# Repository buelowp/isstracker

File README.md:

# Use an opaque globe to show the position of the ISS using a laser
This project is going to project the ISS location on a globe showing current position continuously. The system uses a Particle Argon, one stepper motor for longitude rotation, and one servo motor for latitude rotation. It also uses a LOT of other parts listed in the BOM to make this work.

The goal is to provide a good looking device that is accurate and consistent. All of the motors and electronics must be hidden, and all parts must be independently moveable. So, the globe must be able to rotate without changing where the laser is pointing. The laser must work inside the globe independent of the base. The laser must also rotate 360 degrees longitude. The ISS does not go above or below ~60 degrees latitude, so a simple servo can be used for that.

A Particle project named isstracker

I found a similar project using an ESP8266 about 5 years ago and I was intrigued. So, I started hacking something up, but my requirements became much more complex than the original project. I wanted full rotation and to be able to *spin* the globe sitting on a base without changing where the location of the point showing the ISS.

It uses two independent sliprings which provide the ability to rotate the globe and the armature holding the laser without losing precision. It uses one 200 step NEMA stepper for longitude, and one 160 degree servo for the latitiude. The laser is from Sparkfun, but any laser that can be powered by 3 volts would work.

Pictures to follow

## Building it

Instructions to follow

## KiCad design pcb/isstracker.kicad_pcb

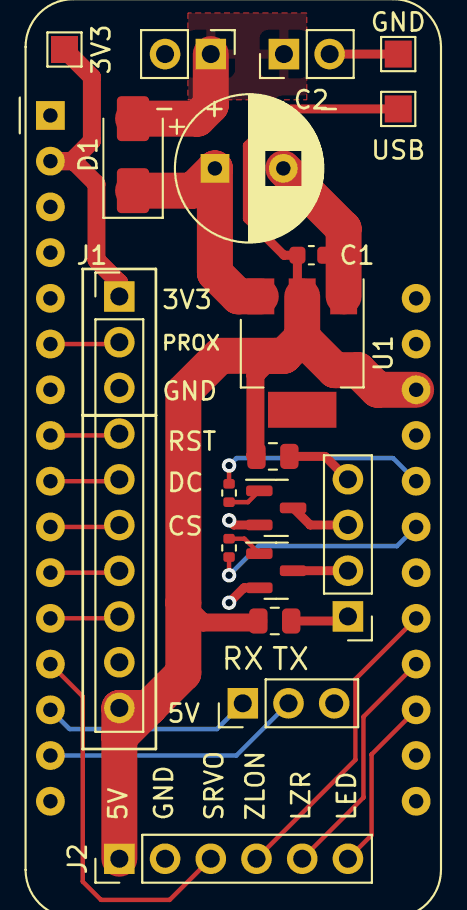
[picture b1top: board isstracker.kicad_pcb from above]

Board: 2 copper layers, 20 parts (0 on the bottom side), 25 nets.

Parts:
A1: Adafruit_Feather_Generic; Adafruit_Feather
C1: 220pf; C_0603_1608Metric
C2: 330uf; CP_Radial_D8.0mm_P3.80mm
D1: D_Schottky; D_SMA
J1: Display; PinHeader_1x10_P2.54mm_Vertical
J2: Control; PinHeader_1x06_P2.54mm_Vertical
J3: POWER; PinHeader_1x02_P2.54mm_Vertical
J4: Error LED; PinHeader_1x04_P2.54mm_Vertical
J5: POWER_OUT; PinHeader_1x02_P2.54mm_Vertical
J6: Conn_01x03_Pin; PinHeader_1x03_P2.54mm_Vertical
Q1, Q2: MMBT2222A; SOT-23
R1, R2: 1k; R_0402_1005Metric
R3, R4: 1k; R_0805_2012Metric
TP1: USB; TestPoint_Pad_1.5x1.5mm
TP2: GND; TestPoint_Pad_1.5x1.5mm
TP3: 3V3; TestPoint_Pad_1.5x1.5mm
U1: CJT1117-5.0; SOT-223

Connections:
+3V3: A1.2 (3V3), J1.1, TP3.1
CS: A1.10 (A5), J1.6
DC: A1.9 (A4), J1.5
GND: A1.4 (GND), C1.2, C2.2, J1.3, J1.9, J2.2, J3.2, J5.2, J6.3, Q1.2 (E), Q2.2 (E), TP2.1, U1.1 (GND)
LASER: A1.20 (D1), J2.5
LED: A1.19 (D0), J2.6
MOSI: A1.12 (MOSI), J1.8
MOTION: A1.6 (A1), J1.2
MOTOR_ERR: A1.24 (D5), R1.1
unnamed: D1.2 (A), J3.1, J5.1
unnamed: C2.1, D1.1 (K), U1.3 (VI)
unnamed: J4.1, R4.2
unnamed: J4.2, Q2.3 (C)
unnamed: J4.3, Q1.3 (C)
unnamed: J4.4, R3.2
unnamed: Q1.1 (B), R1.2
unnamed: Q2.1 (B), R2.2
RST: A1.8 (A3), J1.4
RX: A1.14 (RX), J6.1
SCK: A1.11 (SCK), J1.7
SERVO: A1.13 (MISO), J2.3
TX: A1.15 (TX), J6.2
USB: A1.26 (USB), C1.1, J1.10, J2.1, R3.1, R4.1, TP1.1, U1.2 (VO)
WIFI_ERR: A1.23 (D4), R2.1
ZLON: A1.21 (D2), J2.4

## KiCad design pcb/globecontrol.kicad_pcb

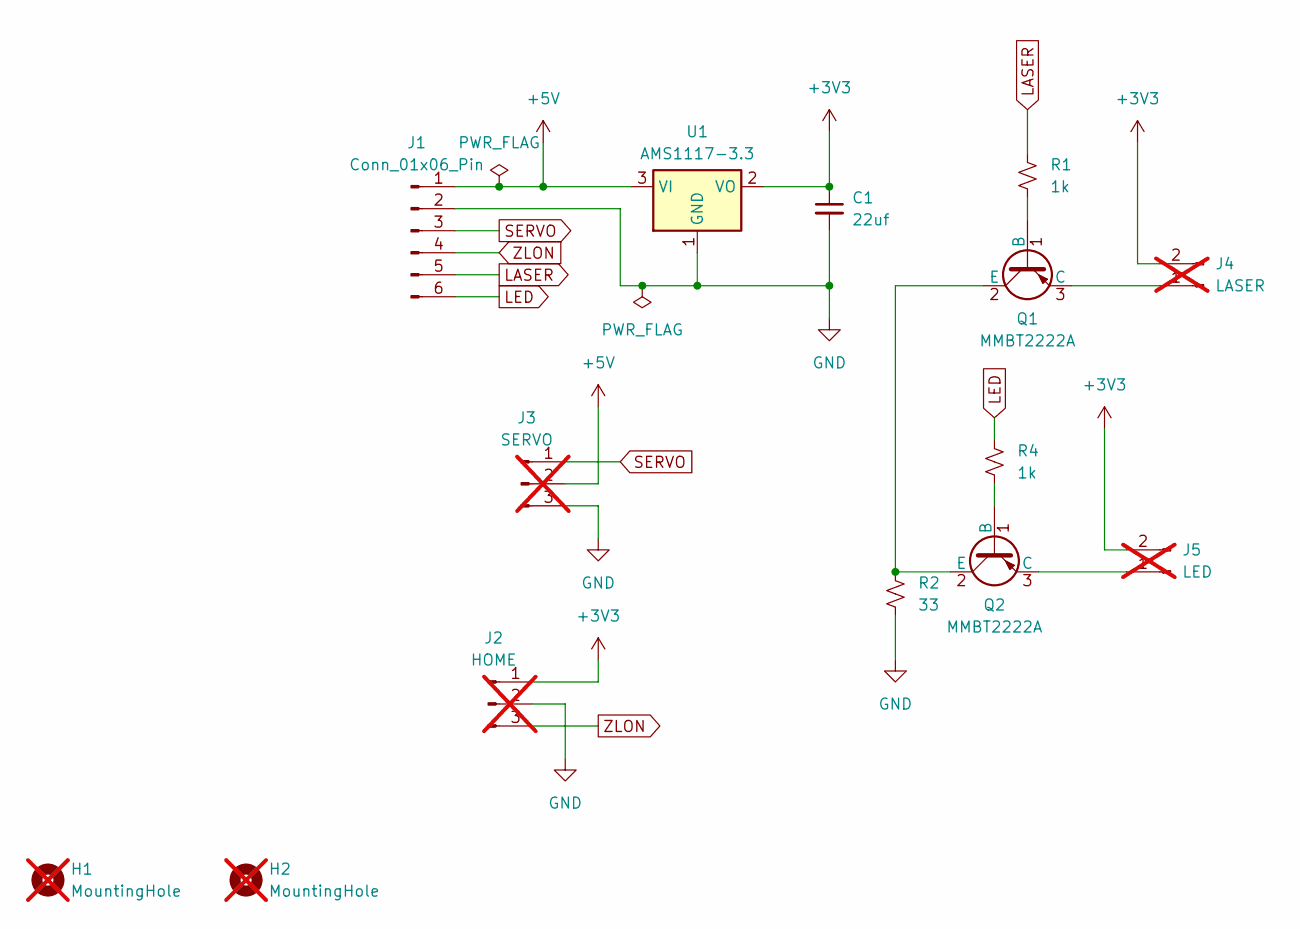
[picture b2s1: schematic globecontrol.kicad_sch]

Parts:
C1: 22uf; C_0603_1608Metric; LCSC C59461
H1, H2: MountingHole; MountingHole_2.1mm; not fitted
J1: Conn_01x06_Pin; PinHeader_1x06_P2.54mm_Vertical
J2: HOME; PinHeader_1x03_P2.54mm_Vertical; not fitted
J3: SERVO; PinHeader_1x03_P2.54mm_Vertical; not fitted
J4: LASER; PinHeader_1x02_P2.54mm_Vertical; not fitted
J5: LED; PinHeader_1x02_P2.54mm_Vertical; not fitted
Q1: MMBT2222A; SOT-23; LCSC C8550
Q2: MMBT2222A; SOT-23; LCSC C8512
R1, R4: 1k; R_0402_1005Metric; LCSC C105637
R2: 33; R_0805_2012Metric; LCSC C17634
U1: AMS1117-3.3; SOT-223-3_TabPin2; LCSC C6186

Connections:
+3V3: C1.1, J2.1, J4.2, J5.2, U1.2 (VO)
+5V: J1.1, J3.2, U1.3 (VI)
GND: C1.2, J1.2, J2.2, J3.3, R2.1, U1.1 (GND)
LASER: J1.5, R1.1
LED: J1.6, R4.1
unnamed: J4.1, Q1.3 (C)
unnamed: J5.1, Q2.3 (C)
unnamed: Q1.1 (B), R1.2
unnamed: Q1.2 (E), Q2.2 (E), R2.2
unnamed: Q2.1 (B), R4.2
SERVO: J1.3, J3.1
ZLON: J1.4, J2.3

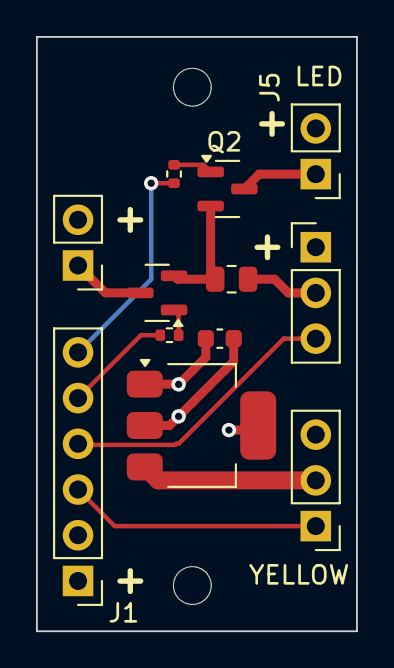
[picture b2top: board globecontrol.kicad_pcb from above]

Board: 4 copper layers, 17.8 x 33.0 mm, 14 parts (0 on the bottom side), 12 nets.

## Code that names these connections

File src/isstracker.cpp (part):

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
#define APP_ID              11

#define MOTION              A1
#define CS                  S3
#define DC                  S4
#define RST                 A5
#define MOTOR_ERR           D6
#define WIFI_ERR            D7
#define SERVO               MISO
#define ZLON                D4
#define LASER               D3
#define LED                 D2

#define ONE_SECOND          1000
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    display.setCursor(0,0);

    display.println("Setting up GPIO");
    pinMode(LASER, OUTPUT);
    pinMode(MOTION, INPUT);
    pinMode(ZLON, INPUT);
    pinMode(MOTOR_ERR, OUTPUT);
    pinMode(WIFI_ERR, OUTPUT);

    Log.info("Applying offsets: LAT: %d, LON: %d", g_latOffset, g_lonOffset);
    display.printf("CAL LAT %d LON %d\n", g_latOffset, g_lonOffset);
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
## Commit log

2020-05-09 Fixed a bug with latitude calculations
2020-05-09 Fixes
    * Fixed a rounding problem
    * Changed a variable name to be more explicit
2021-01-22 Tracker version 45:
    * Cleaning up prints to the display
    * Migrating back to the git src, it's been on it's own for a while
2021-01-22 Updating repo with the non source code portions
2021-01-22 Readme updates
2021-01-22 Fixing PCB to use the new IR sensor instead.
2021-01-24 Version 47:
    * Only wake motor from sleep IFF we are going to move the motor
    * Clean up some extra logging
    * Add LED controls for the globe lighting
    * This includes the first PCB sent out for production at OSHPark
2021-02-06 Version 48
    * Added some colors and made it possible to cycle them on a timer
    * Fixed a display bug
2021-02-07 Updating to the latest PCB to fix breaking issues
    * Fixed capacitor sets for both boards to be larger and polarized on the
    LDO's
    * Fixed left track for motor board as it was 1 pin too short
    * Switched from Declination to Azimuth
    * Moved Azimuth signaling to the internal board to allow for movement
    * Removed resistors on 5V LED signal buffer
2021-02-08 Adding laser control
    * Hookup an NPN to be able to turn the laser on/off via A0
2021-02-09 Adding a duty cycle switch for a Laser
    * Currently unused, the laser I chose does it's own duty cycle, but
    for lasers that can't be on all the time, this will help.
2021-02-14 Lots of changes
    * Dropped LED's and LASER control
    * Renamed DECLINATION to AZIMUTH
    * Moved AZIMUTH control hookup into the globe (it needs to spin freely)
    I couldn't make the LED's fit and shine without casting shadows inside
    the globe. Plus, there wasn't much room, and it required more wires to
    make work. No a critical problem, but the challenges outweighed the
2021-02-17 PCB fixups
    * Bumped PCB revisions
    * Layout changes and some silk screen updates
    * No functionality changes
2021-02-23 Fixups
    * Add the ability to turn the power to the globe on and off via a MOSFET
    * Clean up some of the code
2021-02-23 More fixups
    * Migrate from declination to azimuth
    * Make the globe timeout independent of the display
2021-02-24 More fixups
    * Make the globe power control a toggle, the laser may be more robust
    than I assumed
2021-02-24 Adding a gitignore
2021-02-24 Hookup board revision to 1.6
    * Added a cap in front of the servo as the line to get the 5V is long
    and may not be totally reliable under stress
2021-03-04 Updating to build 53
    * Create a board rev define as I'm testing with an older board. It
    works, but isn't correct
    * Add N/S/E/W to the display to make it more clear where the ISS is
2021-03-06 Layout tweaks
    * Swap pth for smd LED's
    * Move globe power pin to new location
    * Add support hole for motor board if attached via headers
    * Layout fixes for globe with new 4 pin setup
2021-03-06 Control board version 1.7
    * Added a pushbutton to turn the globe back on
    * Began to put globe power control back into app
2021-03-06 Updating to version 54
    * This cleans up globe power control a lot
    * Adds a lot comments to help undestanding
    * Untested as the unit is still down until I update the boards
2021-03-06 Bump control board revision
    * Move pins around for display, motion, and pushbutton
    * Add pushbutton
2021-03-06 Update to version 1.9
    * Fix the FET, it wasn't right
    * New FET in the BOM
    * Put FET on low side and add pulldown on gate
2021-03-06 Adding BOM's
    * New BOM's for tracking components
2021-03-06 Updating LED BOM entry
2021-03-27 Fixes
    * Add globe power using a MOSFET so the laser can be turned on/off
    * Update both board layouts to accomodate new power scheme
    * Fix some component positions in layout
    * Migrate to screw terminals for power on board
2024-05-26 New PCB work
2024-05-26 Migrating to new version 2 of the model
2024-05-26 Added control for an LED for internal illumination
2024-05-26 Updating to add internal globe LED control
2024-08-17 Last updates using the ESP32, moving back to the Photon2
2024-08-17 Migrating from the ESP32 to the Photon2
    * Should make some operations easier
